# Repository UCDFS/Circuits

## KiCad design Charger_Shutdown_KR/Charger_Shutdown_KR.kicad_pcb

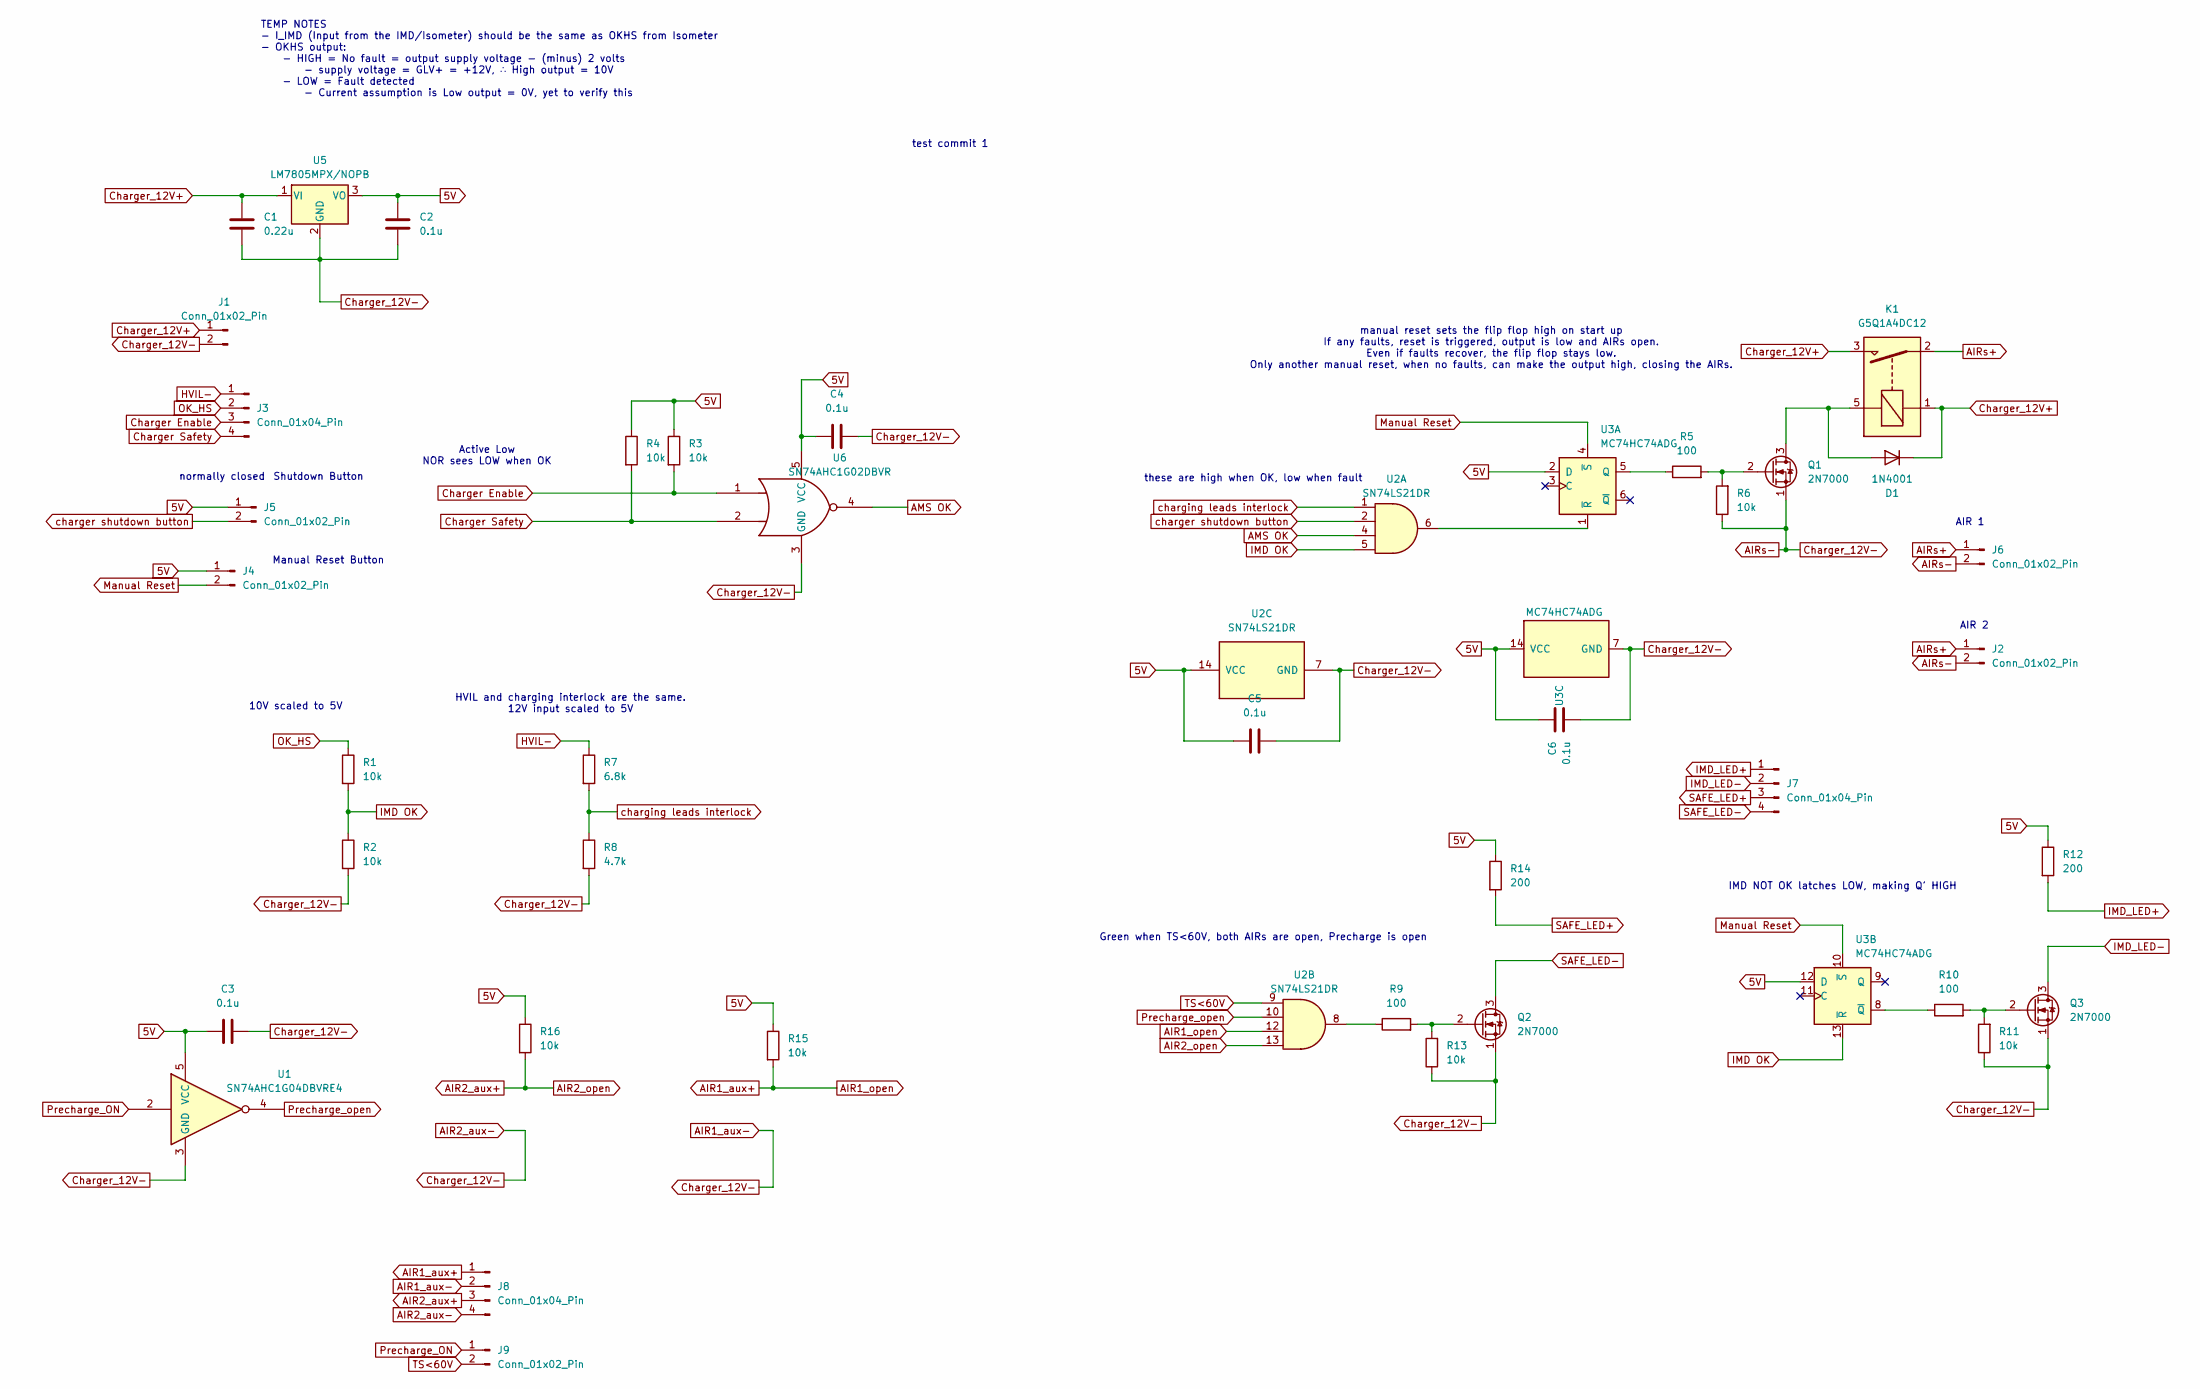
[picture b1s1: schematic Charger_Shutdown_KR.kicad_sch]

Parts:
C1: 0.22u; FA14X7R1H224KNU00; Part Number FA14X7R1H224KNU00
C2, C3, C4, C5, C6: 0.1u; FA18X7R1H104KNU00; Part Number FA18X7R1H104KNU00
D1: 1N4001; D_DO-41_SOD81_P10.16mm_Horizontal; Part Number 1N4001
J1, J2, J4, J5, J6, J9: Conn_01x02_Pin; JST_XH_B2B-XH-A_1x02_P2.50mm_Vertical; Part Number B2B-XH-A
J3, J7, J8: Conn_01x04_Pin; JST_XH_B4B-XH-A_1x04_P2.50mm_Vertical; Part Number B4B-XH-A
K1: G5Q1A4DC12; Relay_SPST_Omron-G5Q-1A; Part Number G5Q1A4DC12
Q1, Q2, Q3: 2N7000; TO-92_Inline; Part Number 2N7000
R1, R2, R3, R4, R6, R11, R13, R15, R16: 10k; R_Axial_DIN0207_L6.3mm_D2.5mm_P10.16mm_Horizontal; Part Number MCF 0.25W 10K
R5, R9, R10: 100; R_Axial_DIN0207_L6.3mm_D2.5mm_P10.16mm_Horizontal; Part Number MCF 0.25W 100R
R7: 6.8k; R_Axial_DIN0207_L6.3mm_D2.5mm_P10.16mm_Horizontal; Part Number MCF 0.25W 6.8K
R8: 4.7k; R_Axial_DIN0207_L6.3mm_D2.5mm_P10.16mm_Horizontal; Part Number MCF 0.25W 4K7
R12, R14: 200; R_Axial_DIN0207_L6.3mm_D2.5mm_P10.16mm_Horizontal; Part Number MCF 0.25W 4K7
U1: SN74AHC1G04DBVRE4; SOT-23-5; Part Number SN74AHC1G04DBVRE4
U2: SN74LS21DR; SOIC-14_3.9x8.7mm_P1.27mm; Part Number SN74LS21DR
U3: MC74HC74ADG; SOIC-14_3.9x8.7mm_P1.27mm; Part Number MC74HC74ADG
U5: LM7805MPX/NOPB; SOT-223-3_TabPin2; Part Number LM7805MPX/NOPB
U6: SN74AHC1G02DBVR; SOT-23-5; Part Number SN74AHC1G02DBVR

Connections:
5V: C2.1, C3.2, C4.1, C5.2, C6.1, J4.1, J5.1, R3.1, R4.1, R12.1, R14.1, R15.1, R16.1, U1.5 (VCC), U2.14 (VCC), U3.2 (D), U3.12 (D), U3.14 (VCC), U5.3 (VO), U6.5 (VCC)
AIR1_aux+: J8.1, R15.2, U2.12
AIR1_aux-: C1.2, C2.2, C3.1, C4.2, C5.1, C6.2, J1.2, J2.2, J6.2, J8.2, J8.4, Q1.1 (S), Q2.1 (S), Q3.1 (S), R2.2, R6.1, R8.2, R11.1, R13.1, U1.3 (GND), U2.7 (GND), U3.7 (GND), U5.2 (GND), U6.3 (GND)
AIR2_aux+: J8.3, R16.2, U2.13
AIRs+: J2.1, J6.1, K1.2
AMS OK: U2.4, U6.4
Charger Enable: J3.3, R3.2, U6.1
Charger Safety: J3.4, R4.2, U6.2
Charger_12V+: C1.1, D1.1 (K), J1.1, K1.1, K1.3, U5.1 (VI)
HVIL-: J3.1, R7.1
IMD OK: R1.2, R2.1, U2.5, U3.13 (~R)
IMD_LED+: J7.1, R12.2
IMD_LED-: J7.2, Q3.3 (D)
Manual Reset: J4.2, U3.4 (~S), U3.10 (~S)
unnamed: D1.2 (A), K1.5, Q1.3 (D)
unnamed: Q1.2 (G), R5.2, R6.2
unnamed: Q2.2 (G), R9.2, R13.2
unnamed: Q3.2 (G), R10.2, R11.2
unnamed: R9.1, U2.8
unnamed: R5.1, U3.5 (Q)
unnamed: U2.6, U3.1 (~R)
unnamed: R10.1, U3.8 (~Q)
OK_HS: J3.2, R1.1
Precharge_ON: J9.1, U1.2
Precharge_open: U1.4, U2.10
SAFE_LED+: J7.3, R14.2
SAFE_LED-: J7.4, Q2.3 (D)
TS<60V: J9.2, U2.9
charger shutdown button: J5.2, U2.2
charging leads interlock: R7.2, R8.1, U2.1

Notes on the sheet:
test commit 1
10V scaled to 5V
AIR 2
manual reset sets the flip flop high on start up If any faults, reset is triggered, output is low and AIRs open. Even if faults recover, the flip flop stays low. Only another manual reset, when no faults, can make the output high, closing the AIRs.
AIR 1
Green when TS<60V, both AIRs are open, Precharge is open
Manual Reset Button
these are high when OK, low when fault
Active Low NOR sees LOW when OK
normally closed
TEMP NOTES - I_IMD (Input from the IMD/Isometer) should be the same as OKHS from Isometer - OKHS output: - HIGH = No fault = output supply voltage - (minus) 2 volts - supply voltage = GLV+ = +12V, ∴ High output = 10V - LOW = Fault detected - Current assumption is Low output = 0V, yet to verify this
Shutdown Button
IMD NOT OK latches LOW, making Q' HIGH
HVIL and charging interlock are the same. 12V input scaled to 5V

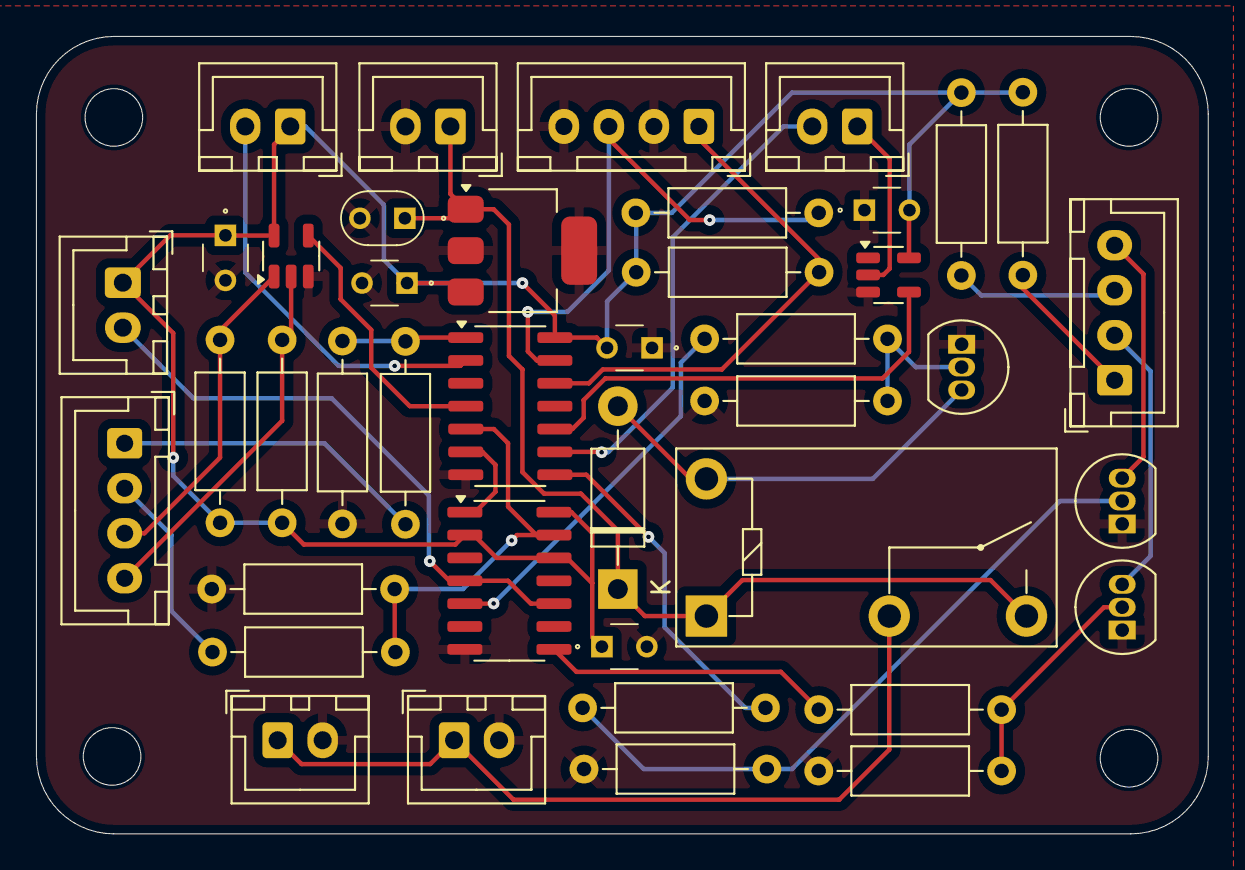
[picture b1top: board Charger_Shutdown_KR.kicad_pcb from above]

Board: 2 copper layers, 65.1 x 44.3 mm, 41 parts (0 on the bottom side), 30 nets.

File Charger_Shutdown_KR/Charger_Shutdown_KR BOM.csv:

"Reference","Value","Part Number","Datasheet","Footprint","Qty","DNP"
"J1,J2,J4,J5,J6,J9","Conn_01x02_Pin","B2B-XH-A","https://www.jst-mfg.com/product/pdf/eng/eXH.pdf","Connector_JST:JST_XH_B2B-XH-A_1x02_P2.50mm_Vertical","6",""
"J3,J7,J8","Conn_01x04_Pin","B4B-XH-A","https://www.jst-mfg.com/product/pdf/eng/eXH.pdf","Connector_JST:JST_XH_B4B-XH-A_1x04_P2.50mm_Vertical","3",""
"D1","1N4001","1N4001","http://www.vishay.com/docs/88503/1n4001.pdf","Diode_THT:D_DO-41_SOD81_P10.16mm_Horizontal","1",""
"C1","0.22u","FA14X7R1H224KNU00","http://www.farnell.com/datasheets/2923220.pdf","FA14_Capacitor:FA14X7R1H224KNU00","1",""
"C2,C3,C4,C5,C6","0.1u","FA18X7R1H104KNU00","http://www.farnell.com/datasheets/2923220.pdf","FA14_Capacitor:FA18X7R1H104KNU00","5",""
"U2","SN74LS21DR","SN74LS21DR","http://www.ti.com/lit/gpn/sn74LS21","Package_SO:SOIC-14_3.9x8.7mm_P1.27mm","1",""
"U3","MC74HC74ADG","MC74HC74ADG","https://www.onsemi.com/download/data-sheet/pdf/mc74hc74a-d.pdf","Package_SO:SOIC-14_3.9x8.7mm_P1.27mm","1",""
"U5","LM7805MPX/NOPB","LM7805MPX/NOPB","https://www.ti.com/lit/gpn/lm7800","Package_TO_SOT_SMD:SOT-223-3_TabPin2","1",""
"U1","SN74AHC1G04DBVRE4","SN74AHC1G04DBVRE4","https://www.ti.com/lit/gpn/sn74ahc1g04","Package_TO_SOT_SMD:SOT-23-5","1",""
"U6","SN74AHC1G02DBVR","SN74AHC1G02DBVR","https://www.ti.com/lit/ds/symlink/sn74ahc1g02.pdf?ts=1738520903275","Package_TO_SOT_SMD:SOT-23-5","1",""
"Q1,Q2,Q3","2N7000","2N7000","https://www.onsemi.com/download/data-sheet/pdf/nds7002a-d.pdf","Package_TO_SOT_THT:TO-92_Inline","3",""
"K1","G5Q1A4DC12","G5Q1A4DC12","https://www.omron.com/ecb/products/pdf/en-g5q.pdf","Relay_THT:Relay_SPST_Omron-G5Q-1A","1",""
"R1,R2,R3,R4,R6,R11,R13,R15,R16","10k","MCF 0.25W 10K","https://www.farnell.com/datasheets/3436052.pdf?_gl=1*j4k0i6*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","Resistor_THT:R_Axial_DIN0207_L6.3mm_D2.5mm_P10.16mm_Horizontal","9",""
"R5,R9,R10","100","MCF 0.25W 100R","https://www.farnell.com/datasheets/3436052.pdf?_gl=1*j4k0i6*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","Resistor_THT:R_Axial_DIN0207_L6.3mm_D2.5mm_P10.16mm_Horizontal","3",""
"R7","6.8k","MCF 0.25W 6.8K","https://www.farnell.com/datasheets/3436052.pdf?_gl=1*j4k0i6*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","Resistor_THT:R_Axial_DIN0207_L6.3mm_D2.5mm_P10.16mm_Horizontal","1",""
"R8","4.7k","MCF 0.25W 4K7","https://www.farnell.com/datasheets/3436052.pdf?_gl=1*1jvprho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","Resistor_THT:R_Axial_DIN0207_L6.3mm_D2.5mm_P10.16mm_Horizontal","1",""
"R12,R14","200","MCF 0.25W 4K7","https://www.farnell.com/datasheets/3436052.pdf?_gl=1*1jvprho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","Resistor_THT:R_Axial_DIN0207_L6.3mm_D2.5mm_P10.16mm_Horizontal","2",""
